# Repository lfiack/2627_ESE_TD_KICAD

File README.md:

# 2627_ESE_TD_KICAD
2627_ESE_TD_KICAD

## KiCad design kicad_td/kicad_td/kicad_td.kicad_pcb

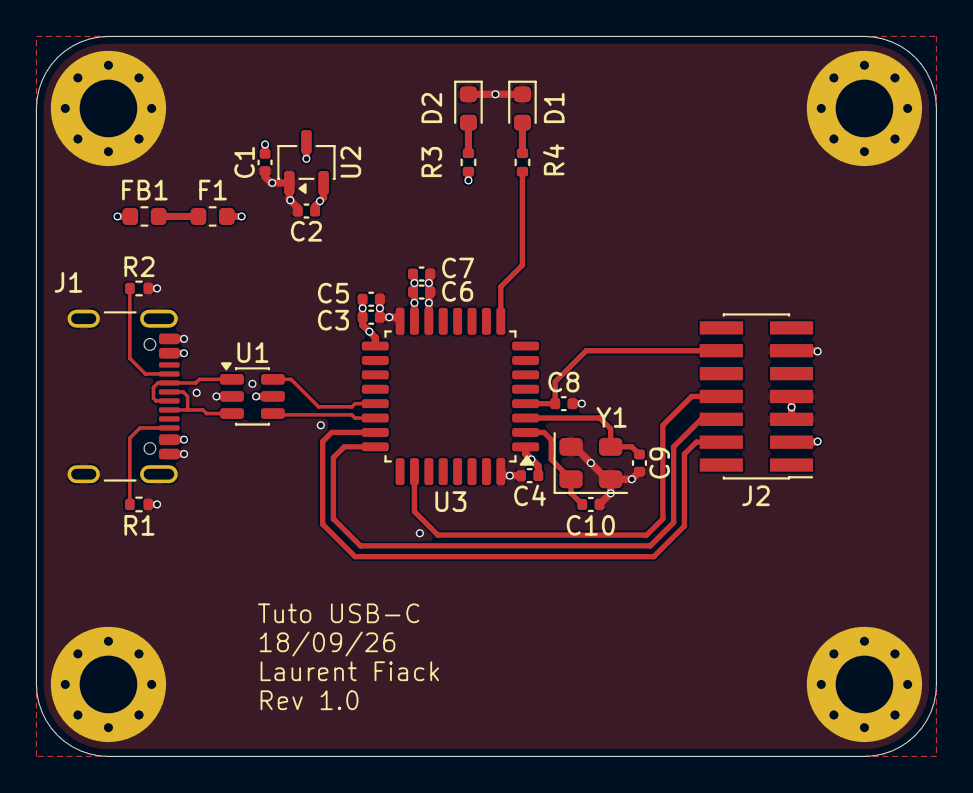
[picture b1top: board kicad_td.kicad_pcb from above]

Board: 4 copper layers, 50.0 x 40.0 mm, 28 parts (0 on the bottom side), 20 nets.

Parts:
C1, C2, C7: 1u; C_0402_1005Metric
C3, C4, C8: 100n; C_0402_1005Metric
C5: 4u7; C_0402_1005Metric
C6: 10n; C_0402_1005Metric
C9, C10: 10pF; C_0402_1005Metric
D1: STATUS; LED_0603_1608Metric
D2: POWER; LED_0603_1608Metric
F1: 250mA; Fuse_0603_1608Metric
FB1: 120Ω@100MHz; L_0603_1608Metric
H1, H2, H3, H4: MountingHole_Pad; MountingHole_3.2mm_M3_Pad_Via
J1: USB_C_Receptacle_USB2.0_16P; USB_C_Receptacle_GCT_USB4105-xx-A_16P_TopMnt_Horizontal
J2: Conn_ST_STDC14; PinHeader_2x07_P1.27mm_Vertical_SMD
R1, R2: 5k1; R_0402_1005Metric
R3, R4: 1k; R_0402_1005Metric
U1: USBLC6-2SC6; SOT-23-6
U2: XC6206P332MR; SOT-23-3
U3: STM32G431KBTx; LQFP-32_7x7mm_P0.8mm
Y1: 16MHz; Crystal_SMD_EuroQuartz_MT-4Pin_3.2x2.5mm

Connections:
+3.3V: C2.1, C3.1, C4.1, C5.1, C6.1, C7.1, J2.3 (VCC), R3.1, U2.2 (VO), U3.1 (VDD), U3.15 (VDDA), U3.17 (VDD)
+5V: C1.1, F1.2, U2.3 (VI)
/STM32/JCLK/SWCLK: J2.6 (JCLK/SWCLK), U3.24 (PA14)
/STM32/JTDO/SWO: J2.8 (JTDO/SWO), U3.26 (PB3)
/STM32/JTMS/SWDIO: J2.4 (JTMS/SWDIO), U3.23 (PA13)
/STM32/NRST: C8.1, J2.12 (~RST), U3.4 (PG10)
/STM32/STATUS: R4.1, U3.9 (PA4)
/STM32/STM32_D+: U1.4 (I/O2), U3.22 (PA12)
/STM32/STM32_D-: U1.6 (I/O1), U3.21 (PA11)
/USB/CC1: J1.A5 (CC1), R2.1
/USB/CC2: J1.B5 (CC2), R1.1
/USB/Fuse: F1.1, FB1.2
/USB/USB_D+: J1.A6 (D+), J1.B6 (D+), U1.3 (I/O2)
/USB/USB_D-: J1.A7 (D-), J1.B7 (D-), U1.1 (I/O1)
GND: C1.2, C2.2, C3.2, C4.2, C5.2, C6.2, C7.2, C8.2, C9.2, C10.2, D1.1 (K), D2.1 (K), H1.1 (1_1), H2.1 (1_1), H3.1 (1_1), H4.1 (1_1), J1.A1 (GND), J1.A12 (GND), J1.B1 (GND), J1.B12 (GND), J1.SH (SHIELD), J2.5 (GND), J2.7 (GND), J2.11 (GNDDetect), R1.2, R2.2, U1.2 (GND), U2.1 (GND), U3.14 (VSSA), U3.16 (VSS), U3.32 (VSS), Y1.2 (G), Y1.4 (G)
unnamed: D1.2 (A), R4.2
unnamed: D2.2 (A), R3.2
unnamed: C10.1, U3.2 (PF0), Y1.1
unnamed: C9.1, U3.3 (PF1), Y1.3
VBUS: FB1.1, J1.A4 (VBUS), J1.A9 (VBUS), J1.B4 (VBUS), J1.B9 (VBUS), U1.5 (VBUS)

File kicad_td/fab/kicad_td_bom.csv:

"Designator","Comment","Footprint","JLCPCB Part #"
"C1,C2,C7","1u","Capacitor_SMD:C_0402_1005Metric","C52923"
"C3,C4,C8","100n","Capacitor_SMD:C_0402_1005Metric","C1525"
"C5","4u7","Capacitor_SMD:C_0402_1005Metric","C23733"
"C6","10n","Capacitor_SMD:C_0402_1005Metric","C15195"
"C9,C10","10pF","Capacitor_SMD:C_0402_1005Metric","C32949"
"D1","STATUS","LED_SMD:LED_0603_1608Metric","C2286"
"D2","POWER","LED_SMD:LED_0603_1608Metric","C2286"
"F1","250mA","Fuse:Fuse_0603_1608Metric","C151137"
"FB1","120Ω@100MHz","Inductor_SMD:L_0603_1608Metric","C14709"
"J1","USB_C_Receptacle_USB2.0_16P","Connector_USB:USB_C_Receptacle_GCT_USB4105-xx-A_16P_TopMnt_Horizontal","C2765186"
"J2","Conn_ST_STDC14","Connector_PinHeader_1.27mm:PinHeader_2x07_P1.27mm_Vertical_SMD","C3975190"
"R1,R2","5k1","Resistor_SMD:R_0402_1005Metric","C25905"
"R3,R4","1k","Resistor_SMD:R_0402_1005Metric","C11702"
"U1","USBLC6-2SC6","Package_TO_SOT_SMD:SOT-23-6","C7519"
"U2","XC6206P332MR","Package_TO_SOT_SMD:SOT-23-3","C5446"
"U3","STM32G431KBTx","Package_QFP:LQFP-32_7x7mm_P0.8mm","C529357"
"Y1","16MHz","Crystal:Crystal_SMD_EuroQuartz_MT-4Pin_3.2x2.5mm","C13738"
